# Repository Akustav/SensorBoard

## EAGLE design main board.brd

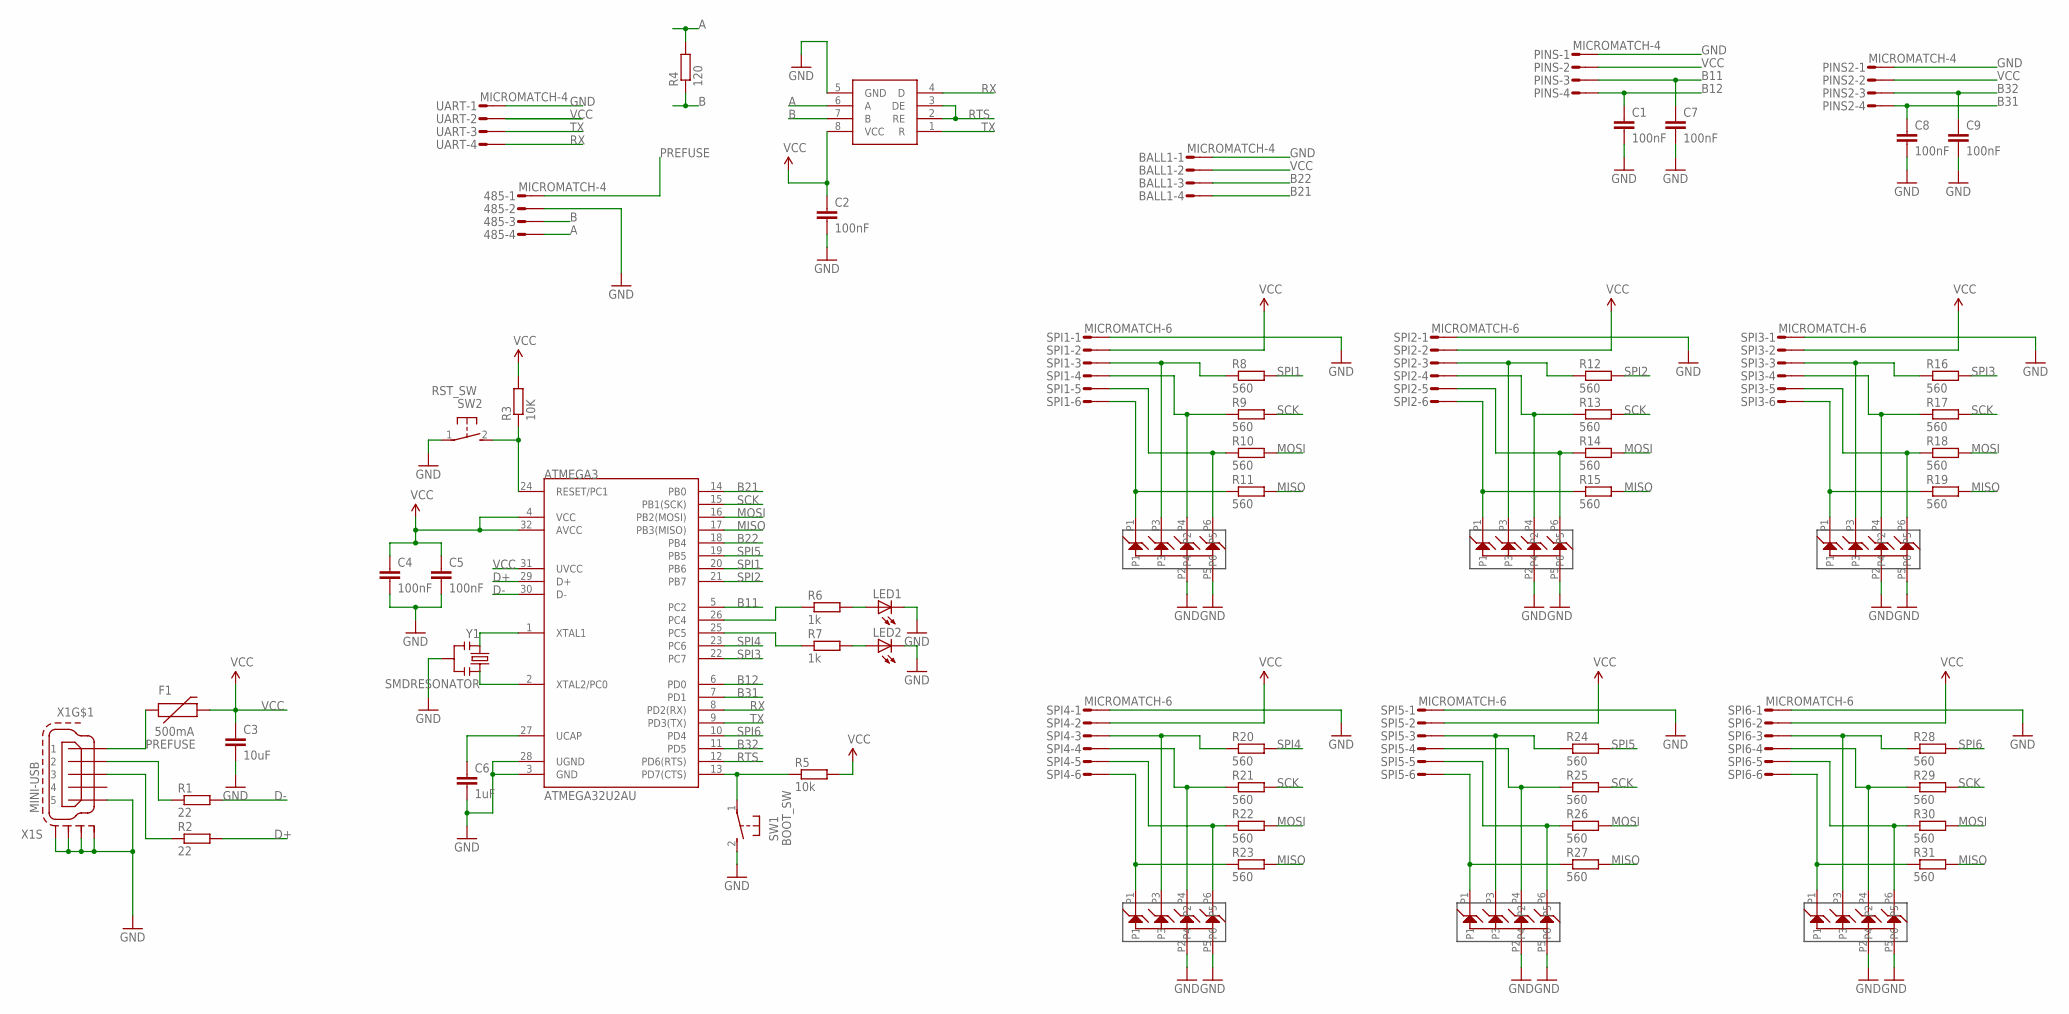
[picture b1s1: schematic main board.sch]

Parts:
485: MICROMATCH-4
ATMEGA3: ATMEGA32U2AU; TQFP32-08
BALL1: MICROMATCH-4
C1, C2, C4, C5, C7, C8, C9: 100nF; C0603
C3: 10uF; C1206K
C6: 1uF; C0603
F1: 500mA; PTC-1206
LED1, LED2: LEDCHIP-LED0603; CHIP-LED0603
PINS, PINS2: MICROMATCH-4
R1, R2: 22; R0603
R3: 10K; R0603
R4: 120; R0603
R5: 10k; R0603
R6, R7: 1k; R0603
R8, R9, R10, R11, R12, R13, R14, R15, R16, R17, R18, R19, R20, R21, R22, R23, R24, R25, R26, R27, R28, R29, R30, R31: 560; R0603
SPI1, SPI2, SPI3, SPI4, SPI5, SPI6: MICROMATCH-6
SW1: BOOT_SW; SMD-TACT-3.9X2.9
SW2: RST_SW; SMD-TACT-3.9X2.9
U$1, U$2, U$3, U$4, U$5, U$6: ESDAXX6LSS; ESDAXX6L
U$7: SN75176BPSR; SOIC
UART: MICROMATCH-4
X1: MINI-USB; 32005-301
Y1: SMDRESONATOR; PBRC-M

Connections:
A: 485.4, R4.2, U$7.6 (A)
B: 485.3, R4.1, U$7.7 (B)
B11: ATMEGA3.5 (PC2), C7.1, PINS.3
B12: ATMEGA3.6 (PD0), C1.1, PINS.4
B21: ATMEGA3.14 (PB0), BALL1.4
B22: ATMEGA3.18 (PB4), BALL1.3
B31: ATMEGA3.7 (PD1), C8.1, PINS2.4
B32: ATMEGA3.11 (PD5), C9.1, PINS2.3
D+: ATMEGA3.29 (D+), R2.2
D-: ATMEGA3.30 (D-), R1.2
GND: 485.2, ATMEGA3.3 (GND), ATMEGA3.28 (UGND), BALL1.1, C1.2, C2.2, C3.2, C4.2, C5.2, C6.2, C7.2, C8.2, C9.2, LED1.C, LED2.C, PINS.1, PINS2.1, SPI1.1, SPI2.1, SPI3.1, SPI4.1, SPI5.1, SPI6.1, SW1.2, SW2.1, U$1.P2, U$1.P5, U$2.P2, U$2.P5, U$3.P2, U$3.P5, U$4.P2, U$4.P5, U$5.P2, U$5.P5, U$6.P2, U$6.P5, U$7.5 (GND), UART.1, X1.5, X1.M1 (S1), X1.M2 (S2), X1.M3 (S3), X1.M4 (S4), Y1.2
MISO: ATMEGA3.17 (PB3(MISO)), R11.2, R15.2, R19.2, R23.2, R27.2, R31.2
MOSI: ATMEGA3.16 (PB2(MOSI)), R10.2, R14.2, R18.2, R22.2, R26.2, R30.2
unnamed: R2.1, X1.3
unnamed: R1.1, X1.2
unnamed: ATMEGA3.1 (XTAL1), Y1.1
unnamed: ATMEGA3.2 (XTAL2/PC0), Y1.3
unnamed: ATMEGA3.13 (PD7(CTS)), R5.1, SW1.1
unnamed: ATMEGA3.24 (RESET/PC1), R3.1, SW2.2
unnamed: R12.1, SPI2.3, U$2.P3
unnamed: R13.1, SPI2.4, U$2.P4
unnamed: ATMEGA3.25 (PC5), R7.1
unnamed: ATMEGA3.27 (UCAP), C6.1
unnamed: ATMEGA3.26 (PC4), R6.1
unnamed: LED1.A, R6.2
unnamed: LED2.A, R7.2
unnamed: R8.1, SPI1.3, U$1.P3
unnamed: R9.1, SPI1.4, U$1.P4
unnamed: R10.1, SPI1.5, U$1.P6
unnamed: R11.1, SPI1.6, U$1.P1
unnamed: R14.1, SPI2.5, U$2.P6
unnamed: R15.1, SPI2.6, U$2.P1
unnamed: R16.1, SPI3.3, U$3.P3
unnamed: R17.1, SPI3.4, U$3.P4
unnamed: R18.1, SPI3.5, U$3.P6
unnamed: R19.1, SPI3.6, U$3.P1
unnamed: R20.1, SPI4.3, U$4.P3
unnamed: R21.1, SPI4.4, U$4.P4
unnamed: R22.1, SPI4.5, U$4.P6
unnamed: R23.1, SPI4.6, U$4.P1
unnamed: R24.1, SPI5.3, U$5.P3
unnamed: R25.1, SPI5.4, U$5.P4
unnamed: R26.1, SPI5.5, U$5.P6
unnamed: R27.1, SPI5.6, U$5.P1
unnamed: R28.1, SPI6.3, U$6.P3
unnamed: R29.1, SPI6.4, U$6.P4
unnamed: R30.1, SPI6.5, U$6.P6
unnamed: R31.1, SPI6.6, U$6.P1
PREFUSE: 485.1, F1.1, X1.1
RTS: ATMEGA3.12 (PD6(RTS)), U$7.2 (RE), U$7.3 (DE)
RX: ATMEGA3.8 (PD2(RX)), U$7.4 (D), UART.4
SCK: ATMEGA3.15 (PB1(SCK)), R9.2, R13.2, R17.2, R21.2, R25.2, R29.2
SPI1: ATMEGA3.20 (PB6), R8.2
SPI2: ATMEGA3.21 (PB7), R12.2
SPI3: ATMEGA3.22 (PC7), R16.2
SPI4: ATMEGA3.23 (PC6), R20.2
SPI5: ATMEGA3.19 (PB5), R24.2
SPI6: ATMEGA3.10 (PD4), R28.2
TX: ATMEGA3.9 (PD3(TX)), U$7.1 (R), UART.3
VCC: ATMEGA3.4 (VCC), ATMEGA3.31 (UVCC), ATMEGA3.32 (AVCC), BALL1.2, C2.1, C3.1, C4.1, C5.1, F1.2, PINS.2, PINS2.2, R3.2, R5.2, SPI1.2, SPI2.2, SPI3.2, SPI4.2, SPI5.2, SPI6.2, U$7.8 (VCC), UART.2

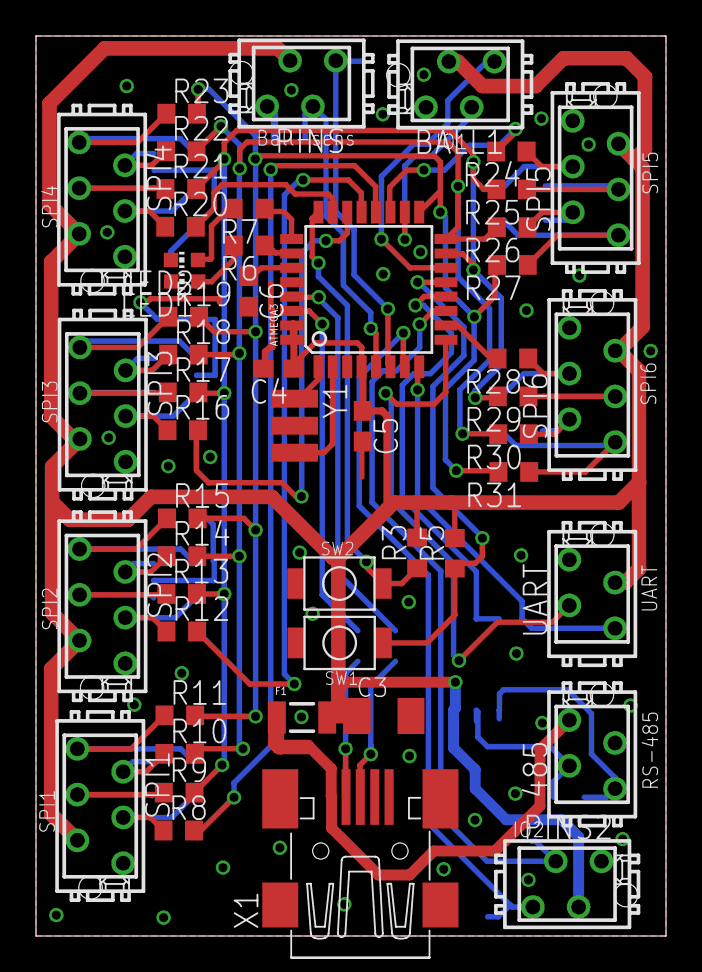
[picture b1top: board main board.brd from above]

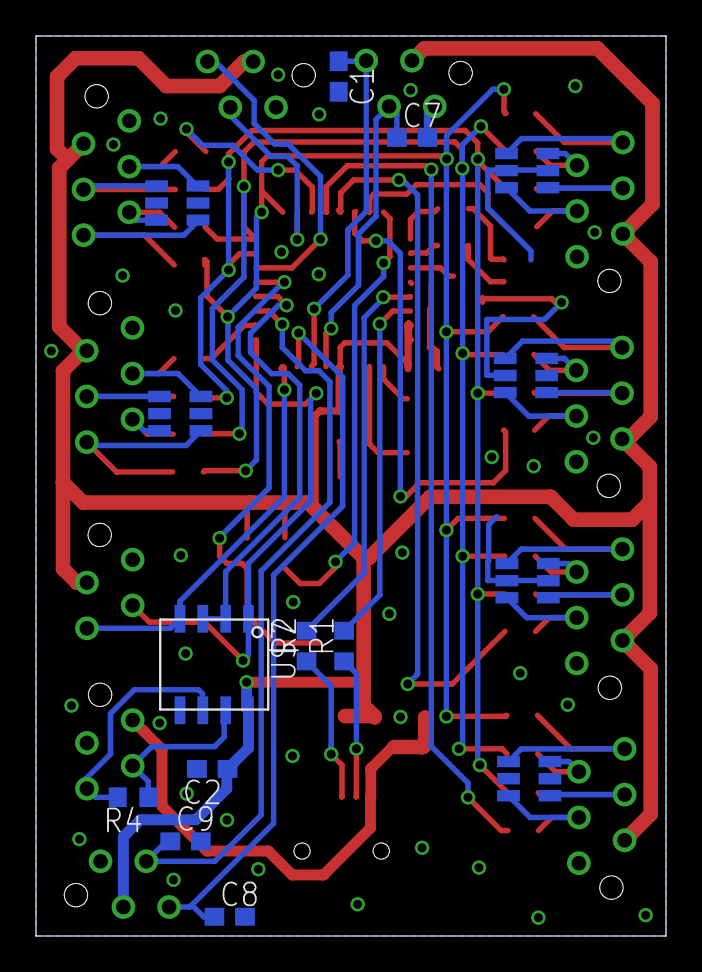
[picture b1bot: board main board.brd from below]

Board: 2 copper layers, 35.0 x 50.0 mm, 66 parts (15 on the bottom side), 60 nets.

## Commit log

2015-04-13 Initial files.
2015-04-13 All pins rooted into micromatches.
2015-04-13 Rotated one micromatch.
2015-04-13 Tweaks to GND plane
2015-04-13 Also added some caps for button or whatever ports.

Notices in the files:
parts and their libraries:
SparkFun: Licensing: CC v3.0 Share-Alike You are welcome to use this library for commercial purposes.
SparkFun-PowerIC: Licensing: Creative Commons ShareAlike 4.0 International - https://creativecommons.org/licenses/by-sa/4.0
